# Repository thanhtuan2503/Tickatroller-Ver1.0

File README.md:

# Introduction to Tickatroller Ver1.0
- Tickatroller Ver1.0 is a control board for line follow car. Tickatroller have some functional blocks such as : encoder reader, esc control, serrvo control and 8 analog input. Besides that, it has jtag and icsp which makes debugging easier.
- Tickatroller use 12V power supply, and user must connect board with power supply before run or burn code.
- This project doesn't include souce code.

<p align="center">
    Side view of 3d render board with KiCad.
</p>

<p align="center">
    Top view of 3d render board with KiCad.
</p>

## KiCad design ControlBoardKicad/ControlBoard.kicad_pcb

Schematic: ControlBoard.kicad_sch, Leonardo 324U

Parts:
1N5824: D_Schottky; SS34_SMC
33uH1: INDUCTOR; L_12x12mm_H8mm
220uF1: CP1; C_Elec_6.3x7.7
220uF2: CP4; C_Elec_6.3x7.7
220uF3: CP2; C_Elec_6.3x7.7
1000uF1: CP3; CP_Elec_10x10.5
C1, C2, C4, C5, C6, C7, C8, C9, C10: 0.1uF; C_0805_2012Metric
C3: 10uF; C_0805_2012Metric
C11, C12: 22pF; C_0805_2012Metric
D1: PWR; LED_0805_2012Metric
D2, D3: LED; LED_0805_2012Metric
D4: SS34; SS34_SMC
D5: SMF05C.TCT; SC70-6
F1: Polyfuse; FerriteBead
FB1, FB2, FB3, FB4, FB5, FB6: Ferrite; FerriteBead
J1: Conn_01x02_Female; TerminalBlock_bornier-2_P5.08mm
Q1, Q2: 2N7002; SOT-23
R1: 1K; R_0805_2012Metric
R2, R3: 470; R_0805_2012Metric
R4, R8, R10, R11: 10k; R_0805_2012Metric
R5: 1M; R_0805_2012Metric
R6, R7, R9: 22; R_0805_2012Metric
R12, R14: 10; R_0805_2012Metric
R13, R15: 10K; R_0805_2012Metric
SW1: ButtonFirst
SW2: SW_Push; SwitchPush
U1: ATMEGA32U4-AU; TQFP-44_10x10mm_Pitch0.8mm
U2: AMS1117
U3: LM2596S; LM2596S-5V
U4: LINE_BLOCK; PinHeader_1x11_P2.54mm_Horizontal
U5: ECD_BLOCK; TerminalBlock_bornier-4_P5.08mm
U6: ESC_BLOCK; TerminalBlock_bornier-3_P5.08mm
U7: SERVO_BLOCK; TerminalBlock_bornier-3_P5.08mm
U8: CODE_INPUT; PinHeader_2x03_P2.54mm_Vertical_SMD
U9: JTAG; PinHeader_2x05_P2.54mm_Vertical_SMD
U10: UART_BLOCK; PinHeader_1x03_P2.54mm_Vertical
X1: USB_OTG; USB_Micro-B_Molex-105017-0001
Y1: Crystal; 2-SMD-5X3

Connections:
+5V: 220uF3.1, C2.1, C3.1, C9.2, D1.2 (A), FB1.2, FB2.2, FB3.2, FB4.2, FB5.2, FB6.2, R2.1, R3.1, R4.2, R10.2, R11.2, U1.6 (UCAP), U2.2 (VOUT), U5.1 (ECD_VCC), U6.2 (VCC), U8.1 (VCC), U9.4 (VCC)
/2596_VCC: 220uF1.1, 1000uF1.1, C1.1, D4.2 (A), U2.3 (VIN), U3.1 (VIN)
/A1: U1.41 ((ADC0)PF0), U4.2 (ADC1)
/A2: U1.40 ((ADC1)PF1), U4.3 (ADC2)
/A3: U1.30 ((ADC13/OC1B/OC4B/PCINT13)PB6), U4.4 (ADC3)
/A4: U1.29 ((ADC12/OC1A/~OC4B/PCINT12)PB5), U4.5 (ADC4)
/A5: U1.28 ((ADC11/PCINT4)PB4), U4.6 (ADC5)
/A6: U1.27 ((T0/OC4D/ADC10)PD7), U4.7 (ADC6)
/A7: U1.26 ((T1/~OC4D/ADC9)PD6), U4.8 (ADC7)
/A8: U1.25 ((ICP2/ADC8)PD4), U4.9 (ADC8)
/CHA: R10.1, U1.18 ((OC0B/SCL/INT0)PD0), U5.3 (ECD_CHA)
/CHB: R11.1, U1.19 ((SDA/INT1)PD1), U5.4 (ECD_CHB)
/D0: U1.22 ((XCK1/~CTS)PD5), U10.3 (Digital)
/D+: R6.1, U1.4 (D+)
/D-: R7.1, U1.3 (D-)
/ESC_PPM: U1.31 ((OC3A/~OC4A)PC6), U6.3 (ESC_PPM)
/MISO: U1.11 ((PDO/MISO/PCINT3)PB3), U8.4 (MISO)
/MOSI: U1.10 ((PDI/MOSI/PCINT2)PB2), U8.3 (MOSI)
/PB0: R12.2, U1.8 ((SS/PCINT0)PB0)
/PE6: R14.2, U1.1 ((INT6/AIN0)PE6)
/PWM_LINE: U1.12 ((OC0A/OC1C/~RTS/PCINT7)PB7), U4.11 (PWM_LINE)
/RX: U1.20 ((RXD/INT2)PD2), U10.1 (RX)
/SCK: U1.9 ((SCLK/PCINT1)PB1), U8.6 (SCK)
/SERVO_PPM: U1.32 ((ICP3/CLK0/OC4A)PC7), U7.3 (SERVO_PPM)
/SER_VCC: 33uH1.2, 220uF2.1, U3.4 (FB), U4.1 (VCC_LINE), U7.2 (SERVO_VCC)
/TCK: U1.39 ((ADC4/TCK)PF4), U9.1 (TCK)
/TDI: U1.36 ((ADC7/TDI)PF7), U9.9 (TDI)
/TDO: U1.37 ((ADC6/TDO)PF6), U9.3 (TDO)
/TMS: U1.38 ((ADC5/TMS)PF5), U9.5 (TMS)
/TX: U1.21 ((TXD/INT3)PD3), U10.2 (TX)
/~RESET: R4.1, SW1.3, U1.13 (~RESET), U8.5 (RST), U9.6 (RESET)
GND: 1N5824.2 (A), 220uF1.2, 220uF2.2, 220uF3.2, 1000uF1.2, C1.2, C2.2, C3.2, C4.2, C5.1, C6.1, C7.1, C8.1, C9.1, C10.1, C11.2, C12.2, D5.2 (GND), J1.1, Q1.2 (S), Q2.2 (S), R1.2, R8.1, R9.1, R13.2, R15.2, SW1.1, U1.5 (UGND), U1.15 (GND), U1.23 (GND), U1.35 (GND), U1.43 (GND), U2.1 (GND), U2.4 (SHIELD), U3.3 (GND), U3.5 (ON/OFF), U3.6 (SHIELD), U4.10 (GND_LINE), U5.2 (ECD_GND), U6.1 (GND), U7.1 (SERVO_GND), U8.2 (GND), U9.2 (GND), U9.10 (GND), X1.5 (GND)
unnamed: 1N5824.1 (K), 33uH1.1, U3.2 (VOUT)
unnamed: C4.1, FB1.1, U1.42 (AREF)
unnamed: C5.2, FB3.1, U1.14 (VCC)
unnamed: C6.2, FB2.1, U1.44 (AVCC)
unnamed: C7.2, FB4.1, U1.34 (VCC)
unnamed: C8.2, FB5.1, U1.24 (AVCC)
unnamed: C10.2, FB6.1, U1.2 (UVCC)
unnamed: C11.1, R5.2, U1.17 (XTAL1), Y1.2
unnamed: C12.1, R5.1, U1.16 (XTAL2), Y1.1
unnamed: D1.1 (K), R1.1
unnamed: D2.1 (K), Q1.3 (D)
unnamed: D2.2 (A), R2.2
unnamed: D3.1 (K), Q2.3 (D)
unnamed: D3.2 (A), R3.2
unnamed: D4.1 (K), SW2.2
unnamed: D5.4 (IO3), R7.2, X1.2 (D-)
unnamed: D5.6 (IO5), R6.2, X1.3 (D+)
unnamed: F1.2, X1.1 (VBUS)
unnamed: J1.2, SW2.1
unnamed: Q1.1 (G), R12.1, R13.1
unnamed: Q2.1 (G), R14.1, R15.1
unnamed: R8.2, U1.33 ((~HWB)PE2)
unnamed: R9.2, X1.6 (Shield)
VBUS: F1.1, U1.7 (VBUS)

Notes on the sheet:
OUTPUT BLOCK
SOURCE BLOCK
DEBUG AND INPUT BLOCK

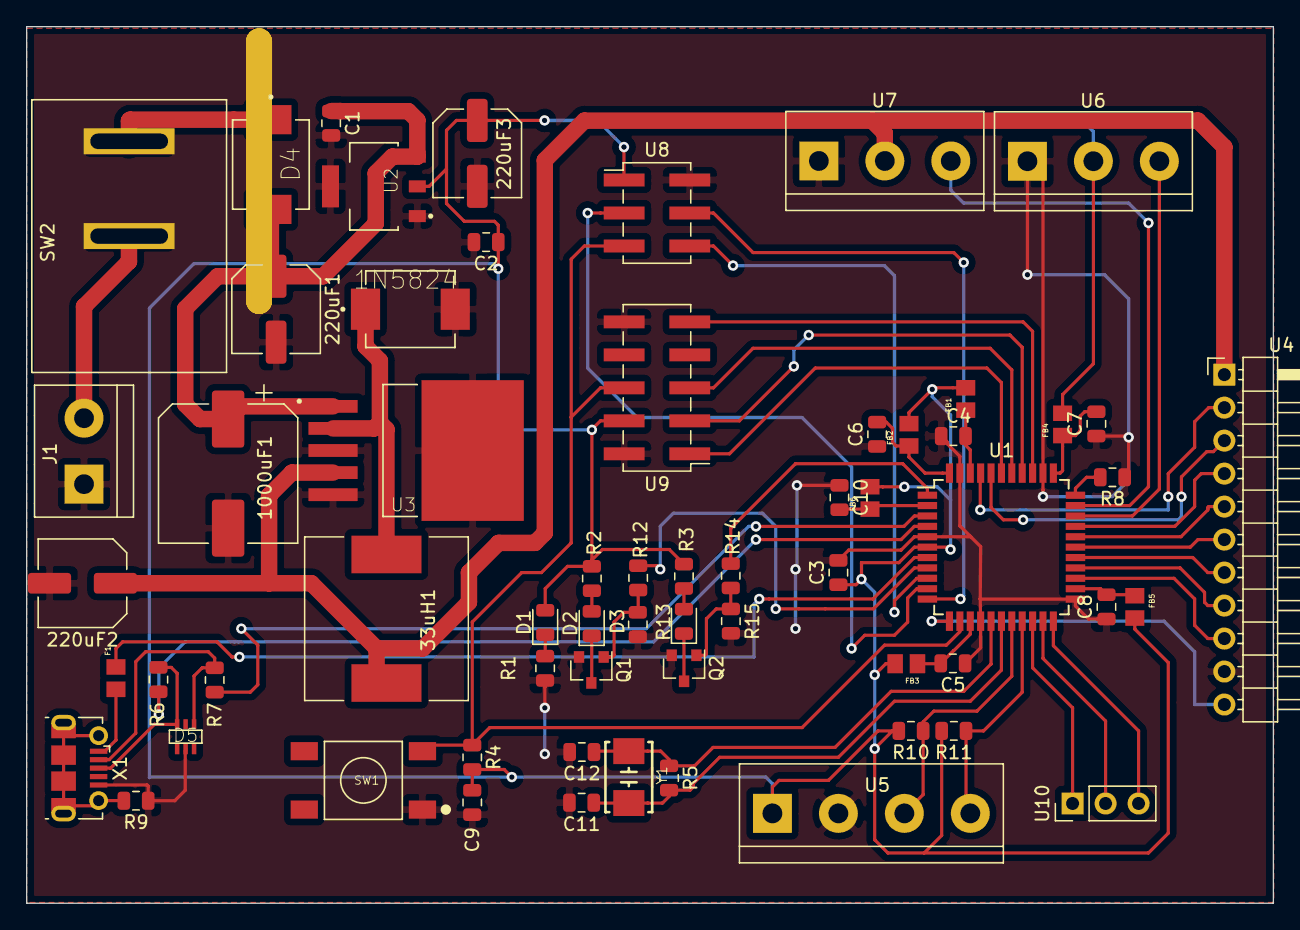
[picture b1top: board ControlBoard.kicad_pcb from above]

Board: 2 copper layers, 96.0 x 67.5 mm, 62 parts (0 on the bottom side), 56 nets.

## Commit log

2020-09-10 First Layout
2020-09-10 Finish Readme
2020-09-10 Finish Readme file
2020-09-10 plot 2 face of pcb board
2020-09-11 Layout Review Finish
2022-01-30 Change work folder
2022-01-30 Update Readme file
